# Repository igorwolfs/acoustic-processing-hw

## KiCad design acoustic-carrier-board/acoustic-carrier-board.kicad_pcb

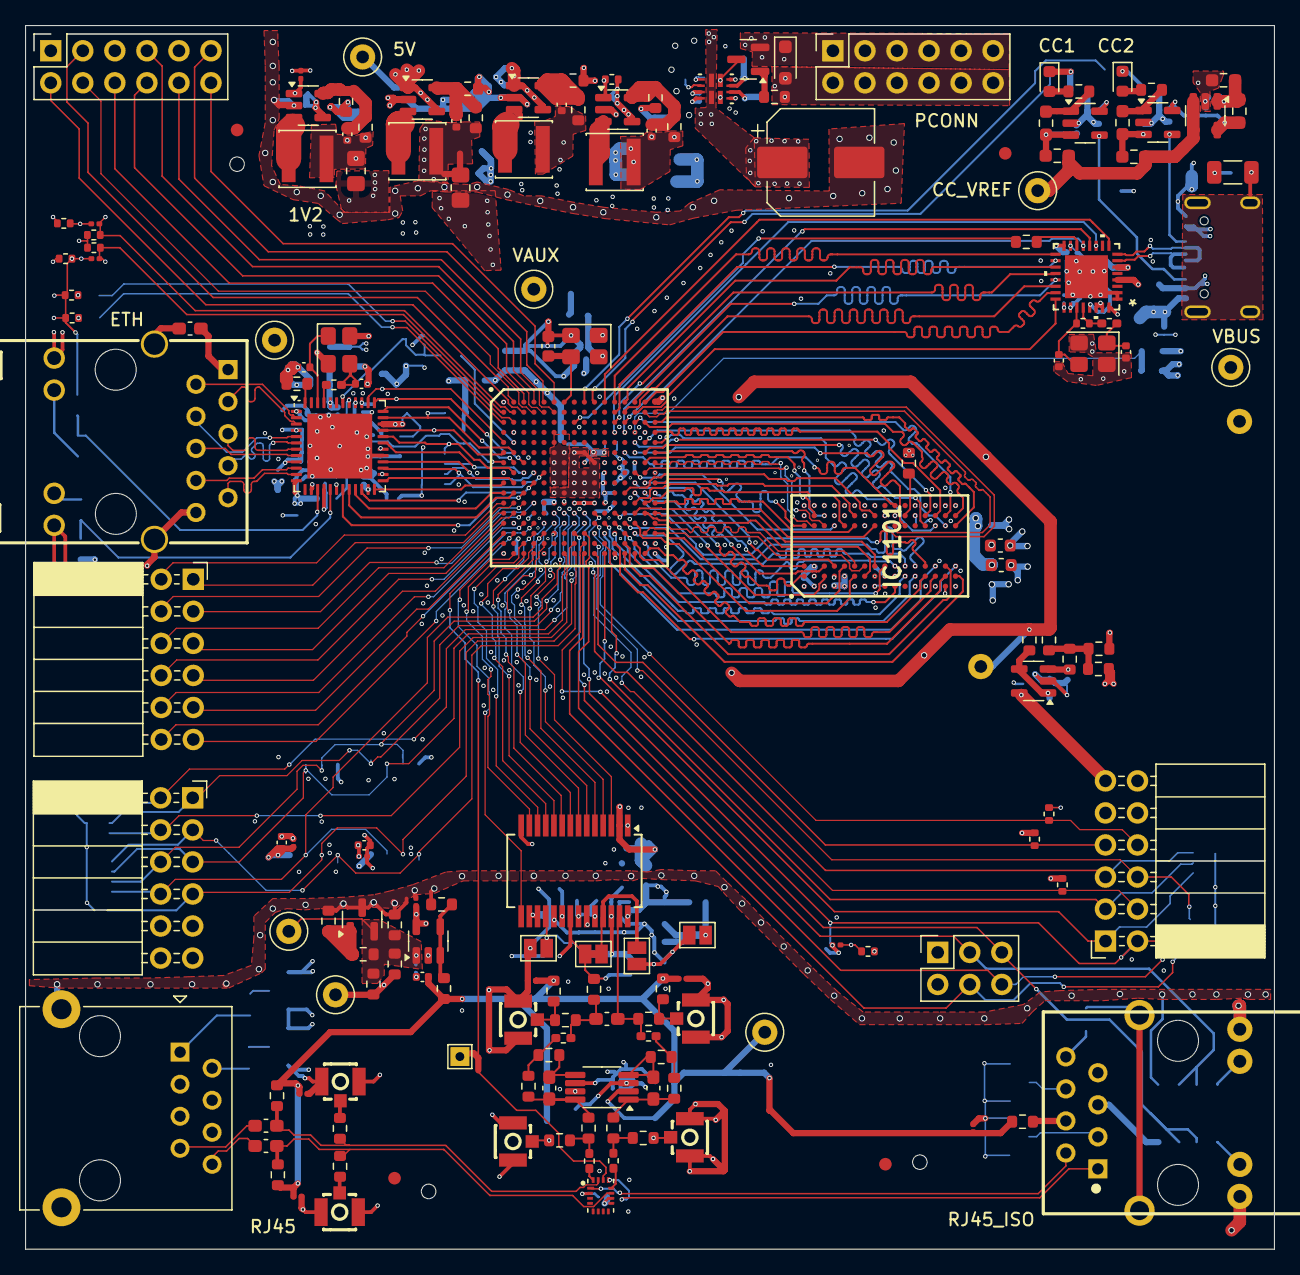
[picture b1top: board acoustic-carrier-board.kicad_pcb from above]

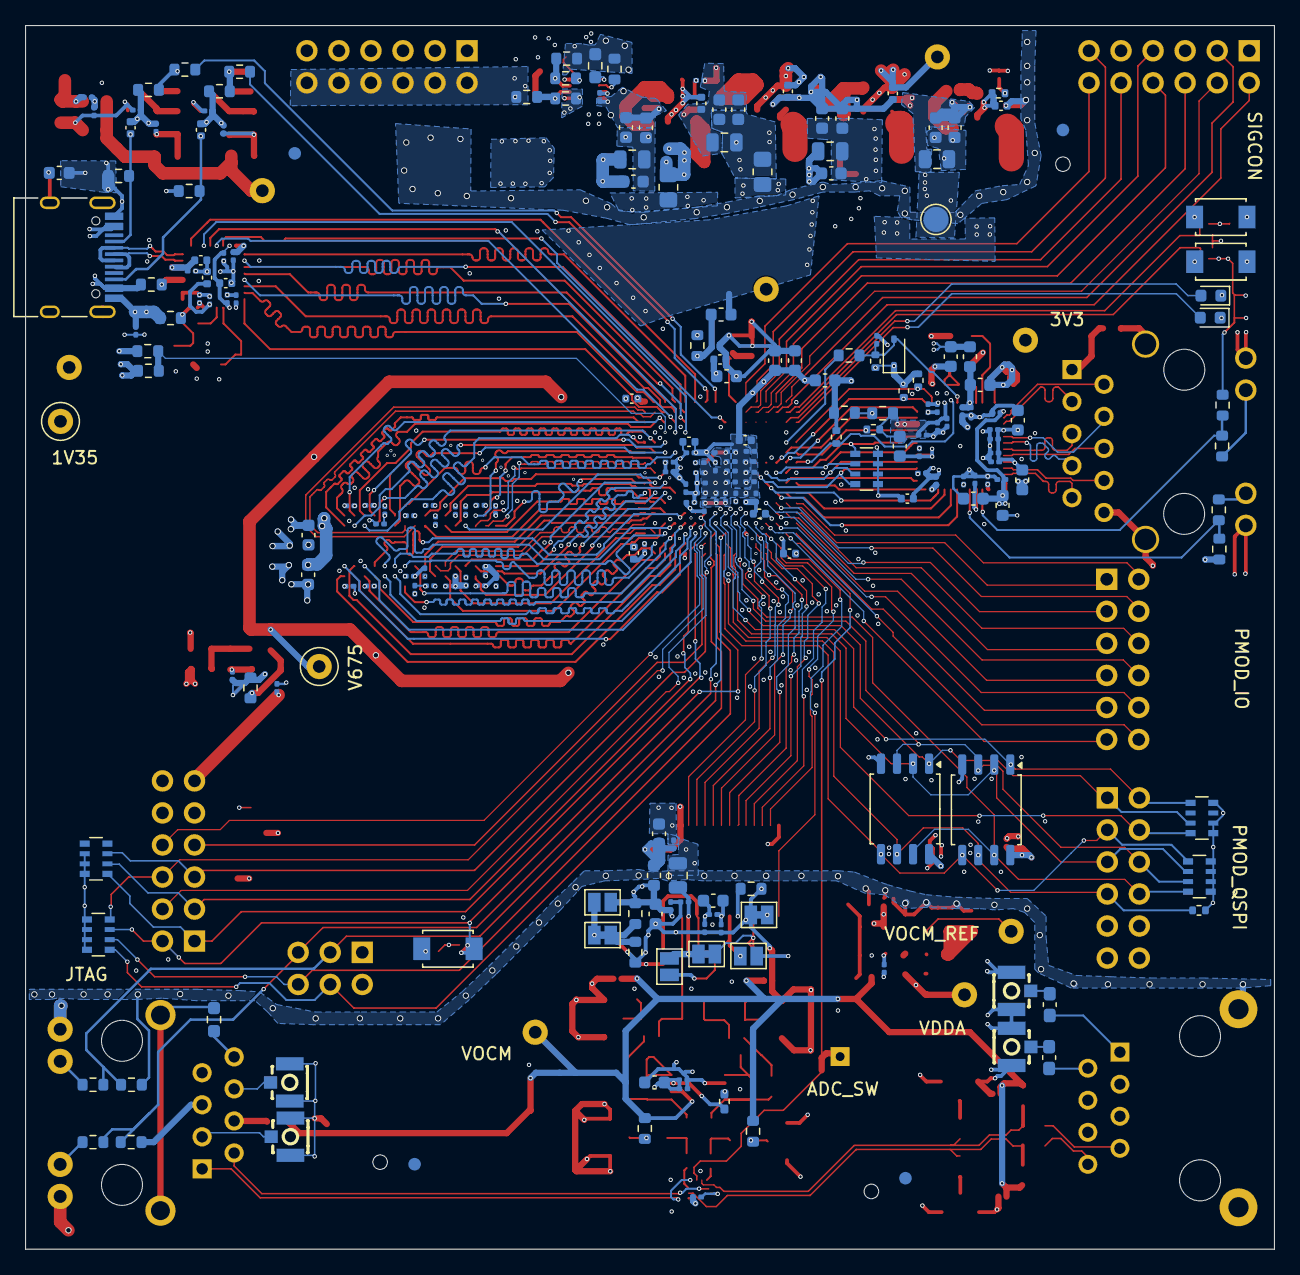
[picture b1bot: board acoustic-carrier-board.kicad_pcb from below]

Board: 6 copper layers, 99.0 x 97.0 mm, 396 parts (228 on the bottom side), 278 nets.

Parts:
C201: 150uF; CP_Elec_8x6.2
C202, C225, C227, C228, C301, C302, C303, C304, C305, C306, C310, C311, C401, C402, C404, C405, C407, C501, C502, C508, C509, C510, C513, C601, C604, C606, C612, C613, C702, C704, C706, C708, C801, C807, C808, C809, C810, C811, C812, C816, C820, C821, C822, C1002, C1003, C1004, C1005, C1008, C1009, C1010, C1011, C1013, C1019, C1021, C1024, C1026, C1027, C1101, C1102, C1103, C1104, C1105, C1106, C1108, C1109, C1110, C1111, C1112, C1116, C1118, C1119, C1120, C1121, C1122, C1123, C1124, C1125, C1203, C1204, C1206, C1207, C1209, C1210, C1216, C1217, C1218, C1219, C1220, C1221, C1222, C1223, C1229: 0.1uF; C_0201_0603Metric
C203, C209, C217, C219: 10pF; C_0402_1005Metric
C204, C205, C206, C210, C211, C214, C215, C220, C221, C222, C307, C308, C309, C1001, C1006, C1007, C1023, C1202, C1205, C1208, C1215, C1224: 10uF; C_0603_1608Metric
C207, C212, C216, C223, C1014: 1uF; C_0805_2012Metric
C208, C213, C218, C224, C312, C403, C406, C503, C512, C603, C611, C701, C705, C707, C813, C814, C819: 4.7uF; C_0402_1005Metric
C226, C507, C511, C602, C703, C802, C817, C825, C1022, C1025, C1114, C1115, C1211, C1212, C1213, C1214, C1225: 10nF; C_0201_0603Metric
C313, C1107, C1113: 22uF; C_0603_1608Metric
C408: 5pF; C_0603_1608Metric
C803, C806, C1227, C1228: 22pF; C_0402_1005Metric
C804, C805: 220pF; C_0402_1005Metric
C815: 1nF; C_1206_3216Metric
C1012, C1015, C1016: 10pF; C_0603_1608Metric_Pad1.08x0.95mm_HandSolder
C1017, C1018, C1028, C1029, C1226: 100 nF +-5%; C_0603_1608Metric_Pad1.08x0.95mm_HandSolder
C1020: 220nF; C_0402_1005Metric
D201: D_Zener; D_SOD-323_HandSoldering
D601, D602, D801, D802: LED_RED; LED_0603_1608Metric
D1201: 1N4148WS; D_SOD-323
FID101, FID102, FID103, FID104, FID105, FID106, FID107, FID108: Fiducial; Fiducial_1mm_Mask2mm
H101, H102, H103: MountingHole; ToolingHole_1.152mm
IC1: ECP5-BGA256; BGA256C80P16X16_1400X1400X170
IC1101: MT41K256M16TW-107_P; BGA96C80P9X16_800X1400X120
J201, J903: Conn_02x06_Odd_Even; PinSocket_2x06_P2.54mm_Vertical
J701: Conn_02x03_Odd_Even; PinSocket_2x03_P2.54mm_Vertical
J702: PMOD_JTAG; PMOD_Pinsocket
J703: PMOD_SPI; PMOD_Pinsocket
J704: PMOD_GPIO; PMOD_Pinsocket
J801: TYPE-C-31-M-12; USB_C_Receptacle_HRO_TYPE-C-31-M-12
J1001, J1002, J1003, J1004, J1005, J1006, J1008, J1009, J1010, J1011: BWU.FL-IPEX1
J1007: 8P8C_Shielded; RJ45_RCH_RC01937
J1201: HR911130A; RJ45-TH_HR911130A
JP1001, JP1004, JP1007, JP1008: SolderJumper_2_Bridged; SolderJumper-2_P1.3mm_Bridged_Pad1.0x1.5mm
JP1002, JP1003, JP1005, JP1006, JP1009, JP1010: SolderJumper_2_Open; SolderJumper-2_P1.3mm_Open_Pad1.0x1.5mm
L201, L202, L203, L204: 2.2uH; L_Changjiang_FNR4018S
L401, L801, L1001, L1101, L1102, L1201, L1202, L1203: 120@100MHz; L_0603_1608Metric
Q201: AO3401A; SOT-23
R201, R202, R604, R606, R704, R705, R707, R1204, R1208, R1212, R1213: 4.7k; R_0402_1005Metric
R203, R216, R225, R226: 24k; R_0603_1608Metric
R204, R803, R811: 100k; R_0603_1608Metric_Pad0.98x0.95mm_HandSolder
R205: 27k; R_0603_1608Metric
R206, R212: 22k; R_0603_1608Metric
R207, R227, R804, R805: 5.1k; R_0603_1608Metric
R208, R209, R217, R301: 0; R_0805_2012Metric_Pad1.20x1.40mm_HandSolder
R210, R211, R213: 100k; R_0603_1608Metric
R215: 75k; R_0603_1608Metric
R218: 30k; R_0603_1608Metric
R219, R223, R224, R401, R815, R830, R1009, R1013, R1021, R1024, R1030, R1031, R1032, R1034, R1036, R1037: 1k; R_0603_1608Metric
R220, R221, R602, R817, R1007, R1008, R1011, R1014, R1022, R1025, R1026, R1039, R1043: 0; R_0603_1608Metric
R222, R801: 220; R_0603_1608Metric
R601, R603, R605, R607, R701: 470; R_0402_1005Metric
R706, R1205: 1k; R_0402_1005Metric
R802, R812: 3k9; R_0603_1608Metric_Pad0.98x0.95mm_HandSolder
R806: 1M; R_0402_1005Metric
R807, R1012, R1015, R1017, R1018, R1020, R1201: 0; R_0402_1005Metric_Pad0.72x0.64mm_HandSolder
R808, R1202: 12k+-1%; R_0603_1608Metric
R809, R810: 33k; R_0603_1608Metric
R813, R821, R1016, R1019: 47; R_0603_1608Metric
R814, R826, R1038: 4.7k; R_0603_1608Metric
R816: 56k; R_0603_1608Metric_Pad0.98x0.95mm_HandSolder
R818: 9k1; R_0603_1608Metric_Pad0.98x0.95mm_HandSolder
R1001: 0; R_0603_1608Metric_Pad0.98x0.95mm_HandSolder
R1002, R1003, R1004, R1005, R1206, R1209: 470; R_0603_1608Metric
R1006, R1010, R1023, R1027, R1028, R1029, R1203, R1207, R1210, R1211: 10k; R_0603_1608Metric
R1033: 75; R_0603_1608Metric
R1035: 1k5; R_0603_1608Metric
R1101: 240; R_0603_1608Metric
RJ1001: HR913550A; RJ45-TH_HR913550A
RN703, RN704, RN708, RN1201: 4x4k7; R_Array_Convex_4x0603
RN707: 4x10k; R_Array_Convex_4x0603
SW602, SW603, SW701: SW_Push; SW_TS-1088-AR02016
TP202, TP205, TP207, TP208, TP209, TP210, TP801, TP1001, TP1011, TP1012: TestPoint; TestPoint_Loop_D1.80mm_Drill1.0mm_Beaded
TP206: TestPoint; TestPoint_Pad_D2.0mm
TP1005: TestPoint; TestPoint_THTPad_1.5x1.5mm_Drill0.7mm
U201: TPS2121RUX; TPS2121
U202, U203, U204, U205: TLV62569DBV; SOT-23-5
U206: OPA376xxDBV; SOT-23-5
U701, U702: W25Q128JVS; SOIC-8_5.3x5.3mm_P1.27mm
U801: USB3300-EZK; QFN32_5X5MC_MCH
U802, U1004: LMV321; SOT-23-5
U803, U804: SOT-23-5
U1001: MS9280; SSOP-28_5.3x10.2mm_P0.65mm
U1002: THS4521IDGK; VSSOP-8_3x3mm_P0.65mm
U1003: DGQ2788AEN-T1-GE4; QFN40P260X180X60-16N_Fv1.2
U1005: TL432DBZ; SOT-23
U1201: KSZ9031RN; QFN-48-1EP_7x7mm_P0.5mm_EP5.15x5.15mm
Y401: Crystal Oscillator; Crystal_SMD_3225-4Pin_3.2x2.5mm
Y801: Crystal_GND24_Small; Crystal_SMD_3225-4Pin_3.2x2.5mm
Y1201: 25MHz; Crystal_SMD_3225-4Pin_3.2x2.5mm

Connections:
+1V2: C209.1, C210.1, C211.1, C212.1, L202.2, R209.1, R211.2
+1V35: C219.1, C220.1, C221.1, C222.1, C223.1, L204.2, R217.1, R218.2
+2V5: C214.1, C215.1, C216.1, C217.1, L203.2, R215.2, R301.1
+3V3: C203.1, C204.1, C205.1, C206.1, C207.1, L201.2, R208.1, R210.2
+5V: C201.1, C208.1, C213.1, C218.1, C224.1, R201.1, R202.1, TP202.1, U201.1 (OUT), U201.8 (OUT), U202.1 (EN), U202.4 (VIN), U203.4 (VIN), U204.1 (EN), U204.4 (VIN), U205.4 (VIN)
/ANALOG-FRONTEND/ADC.CLK: IC1.T2 (PL38D), U1001.15 (CLK)
/ANALOG-FRONTEND/ADC.D0: IC1.M6 (PL47A), U1001.3 (D0)
/ANALOG-FRONTEND/ADC.D1: IC1.P6 (PL47C/LLC_GPLL0T_IN), U1001.4 (D1)
/ANALOG-FRONTEND/ADC.D2: IC1.N6 (PL47B), U1001.5 (D2)
/ANALOG-FRONTEND/ADC.D3: IC1.R5 (PL44A/LDQS44), U1001.6 (D3)
/ANALOG-FRONTEND/ADC.D4: IC1.P5 (PL47D/LLC_GPLL0C_IN), U1001.7 (D4)
/ANALOG-FRONTEND/ADC.D5: IC1.N5 (PL44D), U1001.8 (D5)
/ANALOG-FRONTEND/ADC.D6: IC1.T4 (PL44B/LDQSN44), U1001.9 (D6)
/ANALOG-FRONTEND/ADC.D7: IC1.P4 (PL41A), U1001.10 (D7)
/ANALOG-FRONTEND/ADC.D8: IC1.R4 (PL41C), U1001.11 (D8)
/ANALOG-FRONTEND/ADC.D9: IC1.T3 (PL41D), U1001.12 (D9)
/ANALOG-FRONTEND/ADC.OTR: IC1.R3 (PL41B), U1001.13 (OTR)
/ANALOG-FRONTEND/ADC_AIN+: C1015.2, R1011.1, R1017.2, U1001.27 (AIN)
/ANALOG-FRONTEND/ADC_AIN-: C1015.1, R1014.1, R1020.2, R1022.1
/ANALOG-FRONTEND/ADC_MODE: JP1006.2 (B), JP1008.2 (B), JP1010.2 (B), U1001.23 (MODE)
/ANALOG-FRONTEND/ADC_REFBF: C1001.2, C1002.2, C1004.1, U1001.24 (REFBF)
/ANALOG-FRONTEND/ADC_REFBS: JP1004.1 (A), JP1005.2 (B), U1001.25 (REFBS)
/ANALOG-FRONTEND/ADC_REFSENSE: JP1007.2 (B), JP1009.2 (B), U1001.18 (REFSENSE)
/ANALOG-FRONTEND/ADC_REFTF: C1001.1, C1002.1, C1003.1, U1001.22 (REFTF)
/ANALOG-FRONTEND/ADC_REFTS: JP1002.2 (B), JP1003.2 (B), JP1004.2 (B), R1014.2, U1001.21 (REFTS)
/ANALOG-FRONTEND/ADC_VDDA_2: JP1008.1 (A), R1030.2, R1031.1
/ANALOG-FRONTEND/ADC_VOCM_BUFF: C1009.1, C1010.1, C1011.1, C1020.2, C1026.1, C1027.1, R1006.1, R1010.1, R1023.1, R1027.1, R1028.1, R1029.2, R1033.1, R1039.1, TP1012.1, U1002.2 (V_{OCM})
/ANALOG-FRONTEND/ADC_VOCM_REF: C1022.1, R1032.2, R1034.2, R1035.1, R1037.1, TP1011.1, U1004.1 (+), U1005.2 (K)
/ANALOG-FRONTEND/ADC_VREF: C1013.1, C1014.1, JP1002.1 (A), JP1007.1 (A), U1001.26 (VREF)
/ANALOG-FRONTEND/MAG_ADC_AIN+: RJ1001.2, U1003.1 (NC2)
/ANALOG-FRONTEND/MAG_ADC_AIN-: RJ1001.1, U1003.13 (NC1)
/ANALOG-FRONTEND/RJ45_ADC_AIN+: C1018.2, R1008.1, R1029.1, U1003.15 (NO2)
/ANALOG-FRONTEND/RJ45_ADC_AIN-: C1017.2, R1027.2, R1043.1, U1003.11 (NO1)
/CONNECTORS/PMOD_IO.IO1: IC1.L2 (PL26B/PCLKC6_1), J704.1 (IO1/TMS)
/CONNECTORS/PMOD_IO.IO2: IC1.L4 (PL29C/PL29C), J704.2 (IO2/TDI)
/CONNECTORS/PMOD_IO.IO3: IC1.M2 (PL26D/PCLKC6_0), J704.3 (IO3/TDO)
/CONNECTORS/PMOD_IO.IO4: IC1.N1 (PL32A/LDQS32), J704.4 (IO4/TCK)
/CONNECTORS/PMOD_IO.IO5: IC1.P1 (PL35A), J704.5 (GND)
/CONNECTORS/PMOD_IO.IO6: IC1.P2 (PL32B/LDQSN32), J704.6 (Vcc)
/CONNECTORS/PMOD_IO.IO7: IC1.L1 (PL26A/LDQ32/PCLKT6_1), J704.7 (IO5)
/CONNECTORS/PMOD_IO.IO8: IC1.L3 (PL32C), J704.8 (IO6)
/CONNECTORS/PMOD_IO.IO9: IC1.M1 (PL26C/PCLKT6_0), J704.9 (IO7)
/CONNECTORS/PMOD_IO.IO10: IC1.M3 (PL32D), J704.10 (IO8)
/CONNECTORS/PMOD_IO.IO11: IC1.N3 (PL35D), J704.11 (GND)
/CONNECTORS/PMOD_IO.IO12: IC1.N4 (PL38A/LDQ44), J704.12 (Vcc)
/CONNECTORS/SIGCON.IO1: IC1.B3 (PT4B), J903.2
/CONNECTORS/SIGCON.IO2: IC1.A2 (PT4A), J903.3
/CONNECTORS/SIGCON.IO3: IC1.B4 (PT11B), J903.4
/CONNECTORS/SIGCON.IO4: IC1.A3 (PT6A), J903.6
/CONNECTORS/SIGCON.IO5: IC1.A4 (PT6B), J903.7
/CONNECTORS/SIGCON.IO6: IC1.B5 (PT15B), J903.8
/CONNECTORS/SIGCON.IO7: IC1.B6 (PT22B), J903.10
/CONNECTORS/SIGCON.IO8: IC1.A5 (PT18A), J903.11
/CONNECTORS/SIGCON.IO9: IC1.A6 (PT18B), J903.12
/DDR3/DDR3.A0: IC1.M12 (PR44C), IC1101.N3 (A0)
/DDR3/DDR3.A1: IC1.E16 (PR11D/RDQ8), IC1101.P7 (A1)
/DDR3/DDR3.A2: IC1.P11 (PR47C/LRC_GPLL0T_IN), IC1101.P3 (A2)
/DDR3/DDR3.A3: IC1.T15 (PR38D), IC1101.N2 (A3)
/DDR3/DDR3.A4: IC1.D16 (PR8A/RDQS8), IC1101.P8 (A4)
/DDR3/DDR3.A5: IC1.R14 (PR41B), IC1101.P2 (A5)
/DDR3/DDR3.A6: IC1.C14 (PR2C), IC1101.R8 (A6)
/DDR3/DDR3.A7: IC1.T14 (PR41D), IC1101.R2 (A7)
/DDR3/DDR3.A8: IC1.C15 (PR5B), IC1101.T8 (A8)
/DDR3/DDR3.A9: IC1.R13 (PR41C), IC1101.R3 (A9)
/DDR3/DDR3.A10: IC1.F14 (PR5D), IC1101.L7 (A10/AP)
/DDR3/DDR3.A11: IC1.E15 (PR8B/RDQSN8), IC1101.R7 (A11)
/DDR3/DDR3.A12: IC1.F15 (PR11C), IC1101.N7 (A12/BC#)
/DDR3/DDR3.A13: IC1.R12 (PR44A/RDQS44), IC1101.T3 (A13)
/DDR3/DDR3.A14: IC1.C16 (PR5A), IC1101.T7 (A14)
/DDR3/DDR3.BA0: IC1.N11 (PR47B), IC1101.M2 (BA0)
/DDR3/DDR3.BA1: IC1.E14 (PR5C), IC1101.N8 (BA1)
/DDR3/DDR3.BA2: IC1.N13 (PR38A/RDQ44), IC1101.M3 (BA2)
/DDR3/DDR3.CAS#: IC1.R15 (PR38C), IC1101.K3 (CAS#)
/DDR3/DDR3.CK+: IC1.B16 (PR2A/RDQ8), IC1101.J7 (CK)
/DDR3/DDR3.CK-: IC1.B15 (PR2B/S0_IN), IC1101.K7 (CK#)
/DDR3/DDR3.CKE: IC1.F13 (PR8C), IC1101.K9 (CKE)
/DDR3/DDR3.CS#: IC1.P12 (PR47D/LRC_GPLL0C_IN/RDQ44), IC1101.L2 (CS#)
/DDR3/DDR3.DQ0: IC1.P16 (PR35A), IC1101.E3 (DQ0)
/DDR3/DDR3.DQ1: IC1.L16 (PR26A/PCLKT3_1/RDQ32), IC1101.F7 (DQ1)
/DDR3/DDR3.DQ2: IC1.N14 (PR35D/RDQ32), IC1101.F2 (DQ2)
/DDR3/DDR3.DQ3: IC1.L14 (PR32C), IC1101.F8 (DQ3)
/DDR3/DDR3.DQ4: IC1.M16 (PR26C/PCLKT3_0), IC1101.H3 (DQ4)
/DDR3/DDR3.DQ5: IC1.K13 (PR29A/GR_PCLK3_0), IC1101.H8 (DQ5)
/DDR3/DDR3.DQ6: IC1.M15 (PR26D/PCLKC3_0), IC1101.G2 (DQ6)
/DDR3/DDR3.DQ7: IC1.M14 (PR32D), IC1101.H7 (DQ7)
/DDR3/DDR3.DQ8: IC1.H14 (PR14D), IC1101.D7 (DQ8)
/DDR3/DDR3.DQ9: IC1.K16 (PR23C/PCLKT2_0), IC1101.C3 (DQ9)
/DDR3/DDR3.DQ10: IC1.F16 (PR14A/RDQ20), IC1101.C8 (DQ10)
/DDR3/DDR3.DQ11: IC1.K14 (PR20D/GR_PCLK2_0), IC1101.C2 (DQ11)
/DDR3/DDR3.DQ12: IC1.J16 (PR23A/PCLKT2_1), IC1101.A7 (DQ12)
/DDR3/DDR3.DQ13: IC1.K15 (PR23D/PCLKC2_0/RDQ20), IC1101.A2 (DQ13)
/DDR3/DDR3.DQ14: IC1.G15 (PR14B), IC1101.B8 (DQ14)
/DDR3/DDR3.DQ15: IC1.J14 (PR20C/GR_PCLK2_1), IC1101.A3 (DQ15)
/DDR3/DDR3.LDM: IC1.L15 (PR26B/PCLKC3_1), IC1101.E7 (LDM)
/DDR3/DDR3.LDQS+: IC1.N16 (PR32A/RDQS32), IC1101.F3 (LDQS)
/DDR3/DDR3.LDQS-: IC1.P15 (PR32B/RDQSN32), IC1101.G3 (LDQS#)
/DDR3/DDR3.ODT: IC1.N12 (PR44D), IC1101.K1 (ODT)
/DDR3/DDR3.RAS#: IC1.P13 (PR41A), IC1101.J3 (RAS#)
/DDR3/DDR3.RESET#: IC1.T13 (PR44B/RDQSN44), IC1101.T2 (RESET#)
/DDR3/DDR3.UDM: IC1.J15 (PR23B/PCLKC2_1), IC1101.D3 (UDM)
/DDR3/DDR3.UDQS+: IC1.G16 (PR20A/RDQS20), IC1101.B7 (UDQS#)
/DDR3/DDR3.UDQS-: IC1.H15 (PR20B/RDQSN20), IC1101.C7 (UDQS)
/DDR3/DDR3.WE#: IC1.P14 (PR38B), IC1101.L3 (WE#)
/DDR3/VLPDDR3_CORE: C1101.1, C1103.1, C1104.1, C1105.1, C1106.1, C1107.1, C1118.1, C1119.1, C1120.1, C1124.1, IC1101.B2 (VDD_1), IC1101.D9 (VDD_2), IC1101.G7 (VDD_3), IC1101.K2 (VDD_4), IC1101.K8 (VDD_5), IC1101.N1 (VDD_6), IC1101.N9 (VDD_7), IC1101.R1 (VDD_8), IC1101.R9 (VDD_9), L1101.1
/DDR3/VLPDDR3_DQ: C1102.1, C1108.1, C1109.1, C1110.1, C1111.1, C1112.1, C1113.1, C1116.1, C1123.1, C1125.1, IC1101.A1 (VDDQ_1), IC1101.A8 (VDDQ_2), IC1101.C1 (VDDQ_3), IC1101.C9 (VDDQ_4), IC1101.D2 (VDDQ_5), IC1101.E9 (VDDQ_6), IC1101.F1 (VDDQ_7), IC1101.H2 (VDDQ_8), IC1101.H9 (VDDQ_9), L1102.1
/ETHERNET-PHY/ETH_AC_GND: C1226.1, J1201.1
/ETHERNET-PHY/ETH_GLED_K: J1201.12, R1206.1
/ETHERNET-PHY/ETH_LED_1: R1209.2, R1210.1, U1201.17 (LED1/PHAD0/PME_N1)
/ETHERNET-PHY/ETH_LED_2: R1206.2, R1207.1, U1201.15 (LED2/PHYAD1)
/ETHERNET-PHY/ETH_PHY_A+: J1201.2, U1201.2 (TXRXP_A)
/ETHERNET-PHY/ETH_PHY_A-: J1201.3, U1201.3 (TXRXM_A)
/ETHERNET-PHY/ETH_PHY_B+: J1201.4, U1201.5 (TXRXP_B)
/ETHERNET-PHY/ETH_PHY_B-: J1201.7, U1201.6 (TXRXM_B)
/ETHERNET-PHY/ETH_PHY_C+: J1201.5, U1201.7 (TXRXP_C)
/ETHERNET-PHY/ETH_PHY_C-: J1201.6, U1201.8 (TXRXM_C)
/ETHERNET-PHY/ETH_PHY_D+: J1201.8, U1201.10 (TXRXP_D)
/ETHERNET-PHY/ETH_PHY_D-: J1201.9, U1201.11 (TXRXM_D)
/ETHERNET-PHY/ETH_YLED_K: J1201.13, R1209.1
/ETHERNET-PHY/RGMII_MDIO.CLK: IC1.G2 (PL14B), U1201.36 (MDC)
/ETHERNET-PHY/RGMII_MDIO.DATA: IC1.G3 (PL14C), R1205.1, U1201.37 (MDIO)
/ETHERNET-PHY/RGMII_RX.CLK: IC1.F2 (PL11C), R1203.2, R1211.1, U1201.35 (RX_CLK/PHYAD2)
/ETHERNET-PHY/RGMII_RX.CTL: IC1.F1 (PL14A/LDQ20), R1204.1, U1201.33 (RX_DV/CLK125_EN)
/ETHERNET-PHY/RGMII_RX.D0: IC1.H2 (PL20B/LDQS20), RN1201.1 (R1.1), U1201.32 (RXD0/MODE0)
/ETHERNET-PHY/RGMII_RX.D1: IC1.H3 (PL14D), RN1201.2 (R2.1), U1201.31 (RXD1/MODE1)
/ETHERNET-PHY/RGMII_RX.D2: IC1.H4 (PL17B), RN1201.3 (R3.1), U1201.28 (RXD2/MODE2)
/ETHERNET-PHY/RGMII_RX.D3: IC1.H5 (PL17A), RN1201.4 (R4.1), U1201.27 (RXD3/MODE3)
/ETHERNET-PHY/RGMII_TX.CLK: IC1.J1 (PL23A/PCLKT7_1), U1201.24 (GTX_CLK)
/ETHERNET-PHY/RGMII_TX.CTL: IC1.J2 (PL23B/PCLKC7_1), U1201.25 (TX_EN)
/ETHERNET-PHY/RGMII_TX.D0: IC1.K3 (PL20D), U1201.19 (TXD0)
/ETHERNET-PHY/RGMII_TX.D1: IC1.K2 (PL23D/PCLKC7_0/LDQ20), U1201.20 (TXD1)
/ETHERNET-PHY/RGMII_TX.D2: IC1.K1 (PL23C/PCLKT7_0), U1201.21 (TXD2)
/ETHERNET-PHY/RGMII_TX.D3: IC1.J4 (PL17C), U1201.22 (TXD3)
/ETHERNET-PHY/VDDAH_3V3: C1202.1, C1203.1, C1204.1, L1203.2, U1201.1 (AVDDH), U1201.12 (AVDDH)
/ETHERNET-PHY/VDDAL_1V2: C1208.1, C1209.1, C1210.1, C1211.1, C1212.1, L1201.1, U1201.4 (AVDDL), U1201.9 (AVDDL)
/ETHERNET-PHY/VDDAPLL_1V2: C1205.1, C1206.1, C1207.1, L1202.1, U1201.44 (AVDDL_PLL)
/FPGA-BANK-01/USB.CLK: IC1.C8 (PT35A/PCLKT1_0), R817.2
/FPGA-BANK-01/USB.D0: IC1.B14 (PT67A), U801.24 (DATA0)
/FPGA-BANK-01/USB.D1: IC1.A15 (PT67B), U801.23 (DATA1)
/FPGA-BANK-01/USB.D2: IC1.B13 (PT60A), U801.22 (DATA2)
/FPGA-BANK-01/USB.D3: IC1.A14 (PT65B), U801.21 (DATA3)
/FPGA-BANK-01/USB.D4: IC1.C12 (PT56B), U801.20 (DATA4)
/FPGA-BANK-01/USB.D5: IC1.A13 (PT65A), U801.19 (DATA5)
/FPGA-BANK-01/USB.D6: IC1.B12 (PT56A), U801.18 (DATA6)
/FPGA-BANK-01/USB.D7: IC1.A12 (PT53B), U801.17 (DATA7)
/FPGA-BANK-01/USB.DIR: IC1.D13 (PT62A), U801.12 (DIR)
/FPGA-BANK-01/USB.NXT: IC1.D12 (PT58A), U801.11 (NXT)
/FPGA-BANK-01/USB.RST: IC1.A11 (PT53A), U801.9 (RESET)
/FPGA-BANK-01/USB.STP: IC1.C13 (PT60B), U801.13 (STP)
/FPGA-CONFIG-FLASH/FPGA_CFG0: IC1.N10 (CFG0), J702.10 (IO8), R705.1
/FPGA-CONFIG-FLASH/FPGA_CFG1: IC1.P10 (CFG1), J702.9 (IO7), RN704.4 (R4.1)
/FPGA-CONFIG-FLASH/FPGA_CFG2: IC1.R10 (CFG2), J702.8 (IO6), R707.2
/FPGA-CONFIG-FLASH/FPGA_DONE: IC1.P9 (DONE), J701.6, RN704.2 (R2.1)
/FPGA-CONFIG-FLASH/FPGA_RESETH: C708.1, IC1.R9 (~PROGRAM), J702.7 (IO5), RN704.3 (R3.1), SW701.1
/FPGA-CONFIG-FLASH/JTAG.TCK: IC1.T10 (TCK), J702.4 (IO4/TCK), R704.1
/FPGA-CONFIG-FLASH/JTAG.TDI: IC1.R11 (TDI), J702.2 (IO2/TDI), RN703.2 (R2.1)
/FPGA-CONFIG-FLASH/JTAG.TDO: IC1.M10 (TDO), J702.3 (IO3/TDO), RN703.3 (R3.1)
/FPGA-CONFIG-FLASH/JTAG.TMS: IC1.T11 (TMS), J702.1 (IO1/TMS), RN703.1 (R1.1)
/FPGA-CONFIG-FLASH/QSPI.CSPPIn1: IC1.N8 (~HOLD/DI/BUSY/~CSSPI/PB15A), J703.1 (CSn), RN708.3 (R3.1), U701.1 (~CS)
/FPGA-CONFIG-FLASH/QSPI.CSPPIn2: IC1.M8 (DOUT/~CSO/PB15B), J703.7 (IO1), RN708.1 (R1.1), U702.1 (~CS)
/FPGA-CONFIG-FLASH/QSPI.CSn: IC1.R8 (~CS/~S/PB13A), J703.8 (IO2), RN708.4 (R4.1)
/FPGA-CONFIG-FLASH/QSPI.D0: IC1.T8 (D0/PICO/IO0/PB11B), J703.2 (MOSI/DQ0), RN707.1 (R1.1), U701.5 (DI/IO_{0}), U702.5 (DI/IO_{0})
/FPGA-CONFIG-FLASH/QSPI.D1: IC1.T7 (D1/POCI/IO1/PB11A), J703.3 (MISO/DQ1), RN707.2 (R2.1), U701.2 (DO/IO_{1}), U702.2 (DO/IO_{1})
/FPGA-CONFIG-FLASH/QSPI.D2: IC1.M7 (D2/IO2/PB9B), J703.9 (W/DQ2), RN707.3 (R3.1), U701.3 (~WP/IO_{2}), U702.3 (~WP/IO_{2})
/FPGA-CONFIG-FLASH/QSPI.D3: IC1.N7 (D3/IO3/PB9A), J703.10 (HLD/DQ3), RN707.4 (R4.1), U701.7 (~HOLD/~RESET/IO_{3}), U702.7 (~HOLD/~RESET/IO_{3})
/FPGA-CONFIG-FLASH/QSPI.MCLK: IC1.N9 (MCLK/SCK/CCLK), J703.4 (SCK), R706.2, U701.6 (CLK), U702.6 (CLK)
/FPGA-CONFIG-FLASH/~FPGA_INIT: IC1.T9 (~INIT), J701.4, RN704.1 (R1.1)
/FPGA-DQBANK-67/BUTTON_1: C606.1, IC1.B2 (PL2B), R604.2, SW602.1
/FPGA-DQBANK-67/BUTTON_2: C604.1, IC1.B1 (PL2A/LDQ8), R606.2, SW603.1
/FPGA-DQBANK-67/LED_1: D602.2 (A), IC1.C1 (PL5A)
/FPGA-DQBANK-67/LED_2: D601.2 (A), IC1.C2 (PL5B)
/FPGA-POWER/VAUX: C310.1, C311.1, C312.1, C313.1, IC1.G11 (VCCAUX_1), IC1.L7 (VCCAUX_2), R301.2, TP207.1
/POWER/BP_5V: D201.1 (K), J201.1, J201.3, J201.5, J201.7, J201.9, J201.11, Q201.2 (S)
/POWER/USB_VBUS: C801.1, C807.1, C808.1, C822.1, J801.A4 (VBUS), J801.A9 (VBUS), J801.B4 (VBUS), J801.B9 (VBUS), R226.1, R801.1, R809.1, R816.2, TP210.1, U201.2 (IN2), U802.5 (V+), U803.5 (V+), U804.5 (V+)
/USB-PHY/USBCC_VREF_BUFF: R802.1, R812.1, TP801.1, U802.3 (-), U802.4
/USB-PHY/USB_CC1: C805.1, J801.A5 (CC1), R805.2, U804.4 (-)
/USB-PHY/USB_CC2: C804.1, J801.B5 (CC2), R804.2, U803.4 (-)
/USB-PHY/USB_D+: J801.A6 (DP1), J801.B6 (DP2), U801.7 (DP)
/USB-PHY/USB_D-: J801.A7 (DN1), J801.B7 (DN2), U801.8 (DM)
/USB-PHY/USB_SH: C815.1, J801.S1 (SHIELD), L801.2
/USB-PHY/VDDA_USB1V8: C814.1, C816.1, U801.29 (VDDA1.8)
/USB-PHY/VDD_USB1V8: C819.1, C820.1, C821.1, U801.15 (VDD1.8), U801.26 (VDD1.8)
ETH_REFCLK: IC1.G1 (PL20A/GR_PCLK7_1/LDQSN20), R1213.1, U1201.41 (CLK125_NDO/LED_MODE)
FPGA_ADC_LED0: IC1.M9 (~WRITE/PB18A), J701.5, R1004.2, R1005.2
FPGA_ADC_LED1: IC1.P8 (~CS1/PB13B), J701.3, R1002.2, R1003.1
FPGA_ADC_SW: IC1.R1 (PL35B/VREF1_6), TP1005.1, U1003.14 (IN1-2)
FPGA_CC1: IC1.A10 (PT42B), R814.1
FPGA_CC2: IC1.A9 (PT42A), R826.1
FPGA_USB_SENSE: IC1.D14 (PR2D), R809.2, R810.1
GND: C201.2, C202.2, C204.2, C205.2, C206.2, C207.2, C208.2, C210.2, C211.2, C212.2, C213.2, C214.2, C215.2, C216.2, C218.2, C220.2, C221.2, C222.2, C223.2, C224.2, C225.2, C226.2, C227.2, C228.2, C301.2, C302.2, C303.2, C304.2, C305.2, C306.2, C307.2, C308.2, C309.2, C310.2, C311.2, C312.2, C313.2, C401.2, C402.2, C403.2, C404.2, C405.2, C406.2, C407.2, C408.2, C501.2, C502.2, C503.2, C507.2, C508.2, C509.2, C510.2, C511.2, C512.2, C513.2, C601.2, C602.2, C603.2, C604.2, C606.2, C611.2, C612.2, C613.2, C701.2, C702.2, C703.2, C704.2, C705.2, C706.2, C707.2, C708.2, C801.2, C802.2, C803.1, C804.2, C805.2, C806.1, C807.2, C808.2, C809.2, C810.2, C811.2, C812.2, C813.2, C814.2, C815.2, C816.2, C817.2, C819.2, C820.2, C821.2, C822.2, C825.2, C1003.2, C1004.2, C1005.2, C1006.2, C1007.2, C1008.2, C1009.2, C1010.2, C1011.2, C1013.2, C1014.2, C1019.2, C1020.1, C1021.2, C1022.2, C1023.2, C1024.2, C1025.2, C1026.2, C1027.2, C1101.2, C1102.2, C1103.2, C1104.2, C1105.2, C1106.2, C1107.2, C1108.2, C1109.2, C1110.2, C1111.2, C1112.2, C1113.2, C1114.2, C1115.2, C1116.2, C1118.2, C1119.2, C1120.2, C1121.2, C1122.2, C1123.2, C1124.2, C1125.2, C1202.2, C1203.2, C1204.2, C1205.2, C1206.2, C1207.2, C1208.2, C1209.2, C1210.2, C1211.2, C1212.2, C1213.2, C1214.2, C1215.2, C1216.2, C1217.2, C1218.2, C1219.2, C1220.2, C1221.2, C1222.2, C1223.2, C1224.2, C1225.2, C1226.2, C1227.1, C1228.1, C1229.2, D201.2 (A), IC1.A1 (GND_1), IC1.A16 (GND_2), IC1.D2 (GND_3), IC1.D15 (GND_4), IC1.F8 (GND_5), IC1.F9 (GND_6), IC1.G8 (GND_7), IC1.G10 (GND_8), IC1.H1 (GND_9), IC1.H8 (GND_10), IC1.H9 (GND_11), IC1.H10 (GND_12), IC1.H16 (GND_13), IC1.J8 (GND_14), IC1.J9 (GND_15), IC1.J10 (GND_16), IC1.K6 (GND_17), IC1.K7 (GND_18), IC1.K8 (GND_19), IC1.K9 (GND_20), IC1.K10 (GND_21), IC1.N2 (GND_22), IC1.N15 (GND_23), IC1.T1 (GND_24), IC1.T5 (GND_25), IC1.T12 (GND_26), IC1.T16 (GND_27), IC1101.A9 (VSS_1), IC1101.B1 (VSSQ_1), IC1101.B3 (VSS_2), IC1101.B9 (VSSQ_2), IC1101.D1 (VSSQ_3), IC1101.D8 (VSSQ_4), IC1101.E1 (VSS_3), IC1101.E2 (VSSQ_5), IC1101.E8 (VSSQ_6), IC1101.F9 (VSSQ_7), IC1101.G1 (VSSQ_8), IC1101.G8 (VSS_4), IC1101.G9 (VSSQ_9), IC1101.J2 (VSS_5), IC1101.J8 (VSS_6), IC1101.M1 (VSS_7), IC1101.M9 (VSS_8), IC1101.P1 (VSS_9), IC1101.P9 (VSS_10), IC1101.T1 (VSS_11), IC1101.T9 (VSS_12), J201.2, J201.4, J201.6, J201.8, J201.10, J201.12, J701.1, J702.5 (GND), J702.11 (GND), J703.5 (GND), J703.11 (GND), J801.A1 (GND), J801.A12 (GND), J801.B1 (GND), J801.B12 (GND), J903.1, J903.5, J903.9, J1001.2 (Ext), J1002.2 (Ext), J1003.2 (Ext), J1004.2 (Ext), J1005.2 (Ext), J1006.2 (Ext), J1007.SH, J1008.2 (Ext), J1009.2 (Ext), J1010.2 (Ext), J1011.2 (Ext), J1201.10, J1201.S1 (SHIELD), J1201.S2 (SHIELD), JP1001.1 (A), JP1005.1 (A), JP1009.1 (A), JP1010.1 (A), L801.1, R204.2, R205.1, R206.2, R207.2, R212.1, R213.1, R216.1, R223.2, R224.1, R225.1, R227.2, R601.1, R603.1, R605.2, R607.2, R701.2, R704.2, R705.2, R707.1, R804.1, R805.1, R808.1, R810.2, R815.2, R818.1, R830.2, R1001.1, R1003.2, R1005.1, R1025.1, R1031.2, R1036.1, R1037.2, R1038.2, R1101.2, R1202.2, R1207.2, R1210.2, R1211.2, R1213.2, RJ1001.5, RJ1001.8 (GND), U201.3 (CP2), U201.6 (PR1), U201.12 (GND), U202.2 (GND), U203.2 (GND), U204.2 (GND), U205.2 (GND), U206.2 (V-), U701.4 (GND), U702.4 (GND), U801.1 (GND), U801.2 (GND), U801.33 (EPAD), U802.2 (V-), U803.2 (V-), U804.2 (V-), U1001.1 (AVSS), U1001.14 (DRVSS), U1001.19 (CLAMP), U1002.6 (V_{S-}), U1003.2 (GND), U1004.2 (V-), U1005.3 (A), U1201.29 (VSS), U1201.49 (PAD_GND), Y401.2 (GND), Y801.2, Y801.4, Y1201.2, Y1201.4
unnamed: C806.2, R807.1, Y801.1
unnamed: C1012.1, R1016.2, U1002.4
unnamed: C1016.2, R1019.2, U1002.5
unnamed: C1017.1, J1007.8
unnamed: C1018.1, J1007.7
unnamed: C1028.1, J1007.1
unnamed: C1029.1, J1007.2
unnamed: C1228.2, R1201.1, Y1201.3
unnamed: D601.1 (K), R601.2
unnamed: D602.1 (K), R603.2
unnamed: D801.2 (A), R813.1
unnamed: D801.1 (K), R814.2, R815.1
unnamed: D802.2 (A), R821.1
unnamed: D802.1 (K), R826.2, R830.1
unnamed: C408.1, IC1.A7 (PT29A/PCLKT0_0), Y401.3 (OUT)
unnamed: IC1.E2 (PL8B/LDQSN8), R602.1
unnamed: IC1101.L8 (ZQ), R1101.1
unnamed: J1001.1 (In), R1006.2, R1007.1
unnamed: J1002.1 (In), R1010.2, R1011.2
unnamed: J1003.1 (In), R1008.2
unnamed: C1029.2, J1004.1 (In)
unnamed: J1005.1 (In), R1043.2
unnamed: J1006.1 (In), R1022.2, R1023.2
unnamed: J1008.1 (In), R1026.2, R1028.2
unnamed: J1009.1 (In), RJ1001.3
unnamed: J1010.1 (In), RJ1001.6
unnamed: C1028.2, J1011.1 (In)
unnamed: JP1001.2 (B), U1001.16 (TRISTATE), U1001.17 (STBY)
unnamed: Q201.3 (D), R203.1, U201.7 (IN1)
unnamed: Q201.1 (G), R206.1
unnamed: R219.2, R220.1, R221.2, R223.1
unnamed: R605.1, SW602.2
unnamed: R607.1, SW603.2
unnamed: R701.1, SW701.2
unnamed: R1001.2, RJ1001.13, RJ1001.14
unnamed: R1002.1, RJ1001.11
unnamed: R1004.1, RJ1001.10
unnamed: R1007.2, R1012.2, R1013.2
unnamed: R1009.1, R1016.1, R1017.1
unnamed: R1018.2, R1021.2, R1026.1
unnamed: R1019.1, R1020.1, R1024.2
unnamed: R1039.2, RJ1001.4
unnamed: R205.2, U201.10 (ILM)
unnamed: R203.2, R207.1, U201.5 (OV1)
unnamed: R226.2, R227.1, U201.4 (OV2)
unnamed: C202.1, U201.11 (SS)
unnamed: R204.1, U201.9 (ST)
unnamed: C203.2, R210.1, R212.2, U202.5 (FB)
unnamed: L201.1, U202.3 (SW)
unnamed: C228.1, R201.2, U203.1 (EN)
unnamed: C209.2, R211.1, R213.2, U203.5 (FB)
unnamed: L202.1, U203.3 (SW)
unnamed: C217.2, R215.1, R216.2, U204.5 (FB)
unnamed: L203.1, U204.3 (SW)
unnamed: C227.1, R202.2, U205.1 (EN)
unnamed: C219.2, R218.1, R225.2, U205.5 (FB)
unnamed: L204.1, U205.3 (SW)
unnamed: C226.1, R221.1, U206.3 (+)
unnamed: R222.2, R224.2, U206.1, U206.4 (-)
unnamed: R817.1, U801.14 (CLKOUT)
unnamed: R808.2, U801.32 (RBIAS)
unnamed: R801.2, U801.4 (VBUS)
unnamed: R806.1, R807.2, U801.28 (XI)
unnamed: C803.2, R806.2, U801.27 (XO), Y801.3
unnamed: C802.1, R816.1, R818.2, U802.1 (+)
unnamed: C817.1, R811.1, R812.2, U803.3 (+)
unnamed: R811.2, R813.2, U803.1 (OUT)
unnamed: C825.1, R802.2, R803.1, U804.3 (+)
unnamed: R803.2, R821.2, U804.1 (OUT)
unnamed: R1025.2, U1001.20 (CLAMPIN)
unnamed: C1016.1, R1021.1, R1024.1, U1002.8 (+)
unnamed: C1012.2, R1009.2, R1013.1, U1002.1 (-)
unnamed: R1015.2, U1002.7 (~PD)
unnamed: R1012.1, U1003.12 (COM1)
unnamed: R1018.1, U1003.16 (COM2)
unnamed: R1033.2, R1036.2, U1004.3 (-), U1004.4
unnamed: R1035.2, R1038.1, U1005.1 (REF)
unnamed: R1202.1, U1201.48 (ISET)
unnamed: C1227.2, U1201.46 (XI), Y1201.1
unnamed: R1201.2, U1201.45 (XO)
unnamed: R401.2, Y401.1 (Tri-State)
unnamed: C407.1, L401.2, R401.1, Y401.4 (VDD)
VCORE_3V3: C225.1, C301.1, C302.1, C303.1, C304.1, C305.1, C306.1, C307.1, C308.1, C309.1, C401.1, C402.1, C403.1, C404.1, C405.1, C406.1, C601.1, C602.1, C603.1, C611.1, C612.1, C613.1, C701.1, C702.1, C703.1, C704.1, C705.1, C706.1, C707.1, C809.1, C810.1, C811.1, C812.1, C813.1, C1007.1, C1008.1, C1221.1, C1222.1, C1223.1, C1224.1, C1225.1, D1201.1 (K), IC1.F6 (VCCIO0_1), IC1.F7 (VCCIO0_2), IC1.F10 (VCCIO1_1), IC1.F11 (VCCIO1_2), IC1.G6 (VCC_1), IC1.G7 (VCC_2), IC1.G9 (VCC_3), IC1.H6 (VCCIO7_1), IC1.H7 (VCCIO7_2), IC1.J6 (VCCIO6_1), IC1.J7 (VCCIO6_2), IC1.L6 (VCCIO8), IC1.L8 (VCC_4), IC1.L9 (VCC_5), IC1.L10 (VCC_6), J701.2, J702.6 (Vcc), J702.12 (Vcc), J703.6 (Vcc), J703.12 (Vcc), J1201.11, J1201.14, L401.1, L1001.1, L1203.1, R208.2, R604.1, R606.1, R706.1, R1203.1, R1204.2, R1205.2, R1208.2, R1212.2, RN703.6 (R3.2), RN703.7 (R2.2), RN703.8 (R1.2), RN704.5 (R4.2), RN704.6 (R3.2), RN704.7 (R2.2), RN704.8 (R1.2), RN707.5 (R4.2), RN707.6 (R3.2), RN707.7 (R2.2), RN707.8 (R1.2), RN708.5 (R4.2), RN708.6 (R3.2), RN708.8 (R1.2), RN1201.5 (R4.2), RN1201.6 (R3.2), RN1201.7 (R2.2), RN1201.8 (R1.2), TP205.1, U206.5 (V+), U701.8 (VCC), U702.8 (VCC), U801.6 (VDD3.3), U801.16 (VDD3.3), U801.25 (VDD3.3), U801.30 (VDD3.3), U801.31 (REG_EN), U1001.2 (DRVDD), U1201.16 (DVDDH), U1201.34 (DVDDH), U1201.40 (DVDDH)
VDDA: C1005.1, C1006.1, C1019.1, C1021.1, C1023.1, C1024.1, C1025.1, JP1003.1 (A), JP1006.1 (A), L1001.2, R1015.1, R1030.1, R1032.1, R1034.1, RJ1001.9, RJ1001.12, TP1001.1, U1001.28 (AVDD), U1002.3 (V_{S+}), U1003.10 (V+), U1004.5 (V+)
VETH_1V2: C1213.1, C1214.1, C1215.1, C1216.1, C1217.1, C1218.1, C1219.1, C1220.1, L1201.2, L1202.2, R209.2, TP206.1, U1201.14 (DVDDL), U1201.18 (DVDDL), U1201.23 (DVDDL), U1201.26 (DVDDL), U1201.30 (DVDDL), U1201.39 (DVDDL)
VLPDDR3_1V35: C501.1, C502.1, C503.1, C509.1, C510.1, C511.1, C512.1, IC1.H11 (VCCIO2_1), IC1.J11 (VCCIO2_2), IC1.K11 (VCCIO3_1), IC1.L11 (VCCIO3_2), L1101.2, L1102.2, R217.2, R219.1, TP209.1
VLPDDR3_V675: C507.1, C508.1, C513.1, C1114.1, C1115.1, C1121.1, C1122.1, IC1.G14 (PR14C/VREF1_2), IC1.R16 (PR35B/VREF1_3), IC1101.H1 (VREFDQ), IC1101.M8 (VREFCA), R220.2, R222.1, TP208.1
~ETH_INT: IC1.E1 (PL11D/LDQ8), R1208.1, U1201.38 (INT_N/PME_N2)
~ETH_RESET: C1229.1, D1201.2 (A), R602.2, R1212.1, U1201.42 (RESET_N)

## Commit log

2025-07-28 removed top repos
2025-07-28 simplified repo
2025-07-28 added vhdl
2025-07-29 Created production files
2025-07-29 created latest manufacturing files inside production folder
2025-07-29 minor changes
2025-07-31 reorganised folders
2025-08-03 Modified README, lpddr3 testpoint search
2025-08-03 Modified readme, removed testpoints and stubs, changed simulation folder structure, removed excess length matching
2025-08-03 [docs] Cleanup [README] minor modifications
2025-08-07 added step-files
2025-08-23 order carrier board
2025-08-28 added impedance matching comments,
2025-09-07 added production files for carrier board
2025-09-18 added x-ray inspection pictures, checking pinout validity
2025-10-25 continuing bringup
2025-12-08 modified gitignore
2025-12-08 added submodule IC drivers
